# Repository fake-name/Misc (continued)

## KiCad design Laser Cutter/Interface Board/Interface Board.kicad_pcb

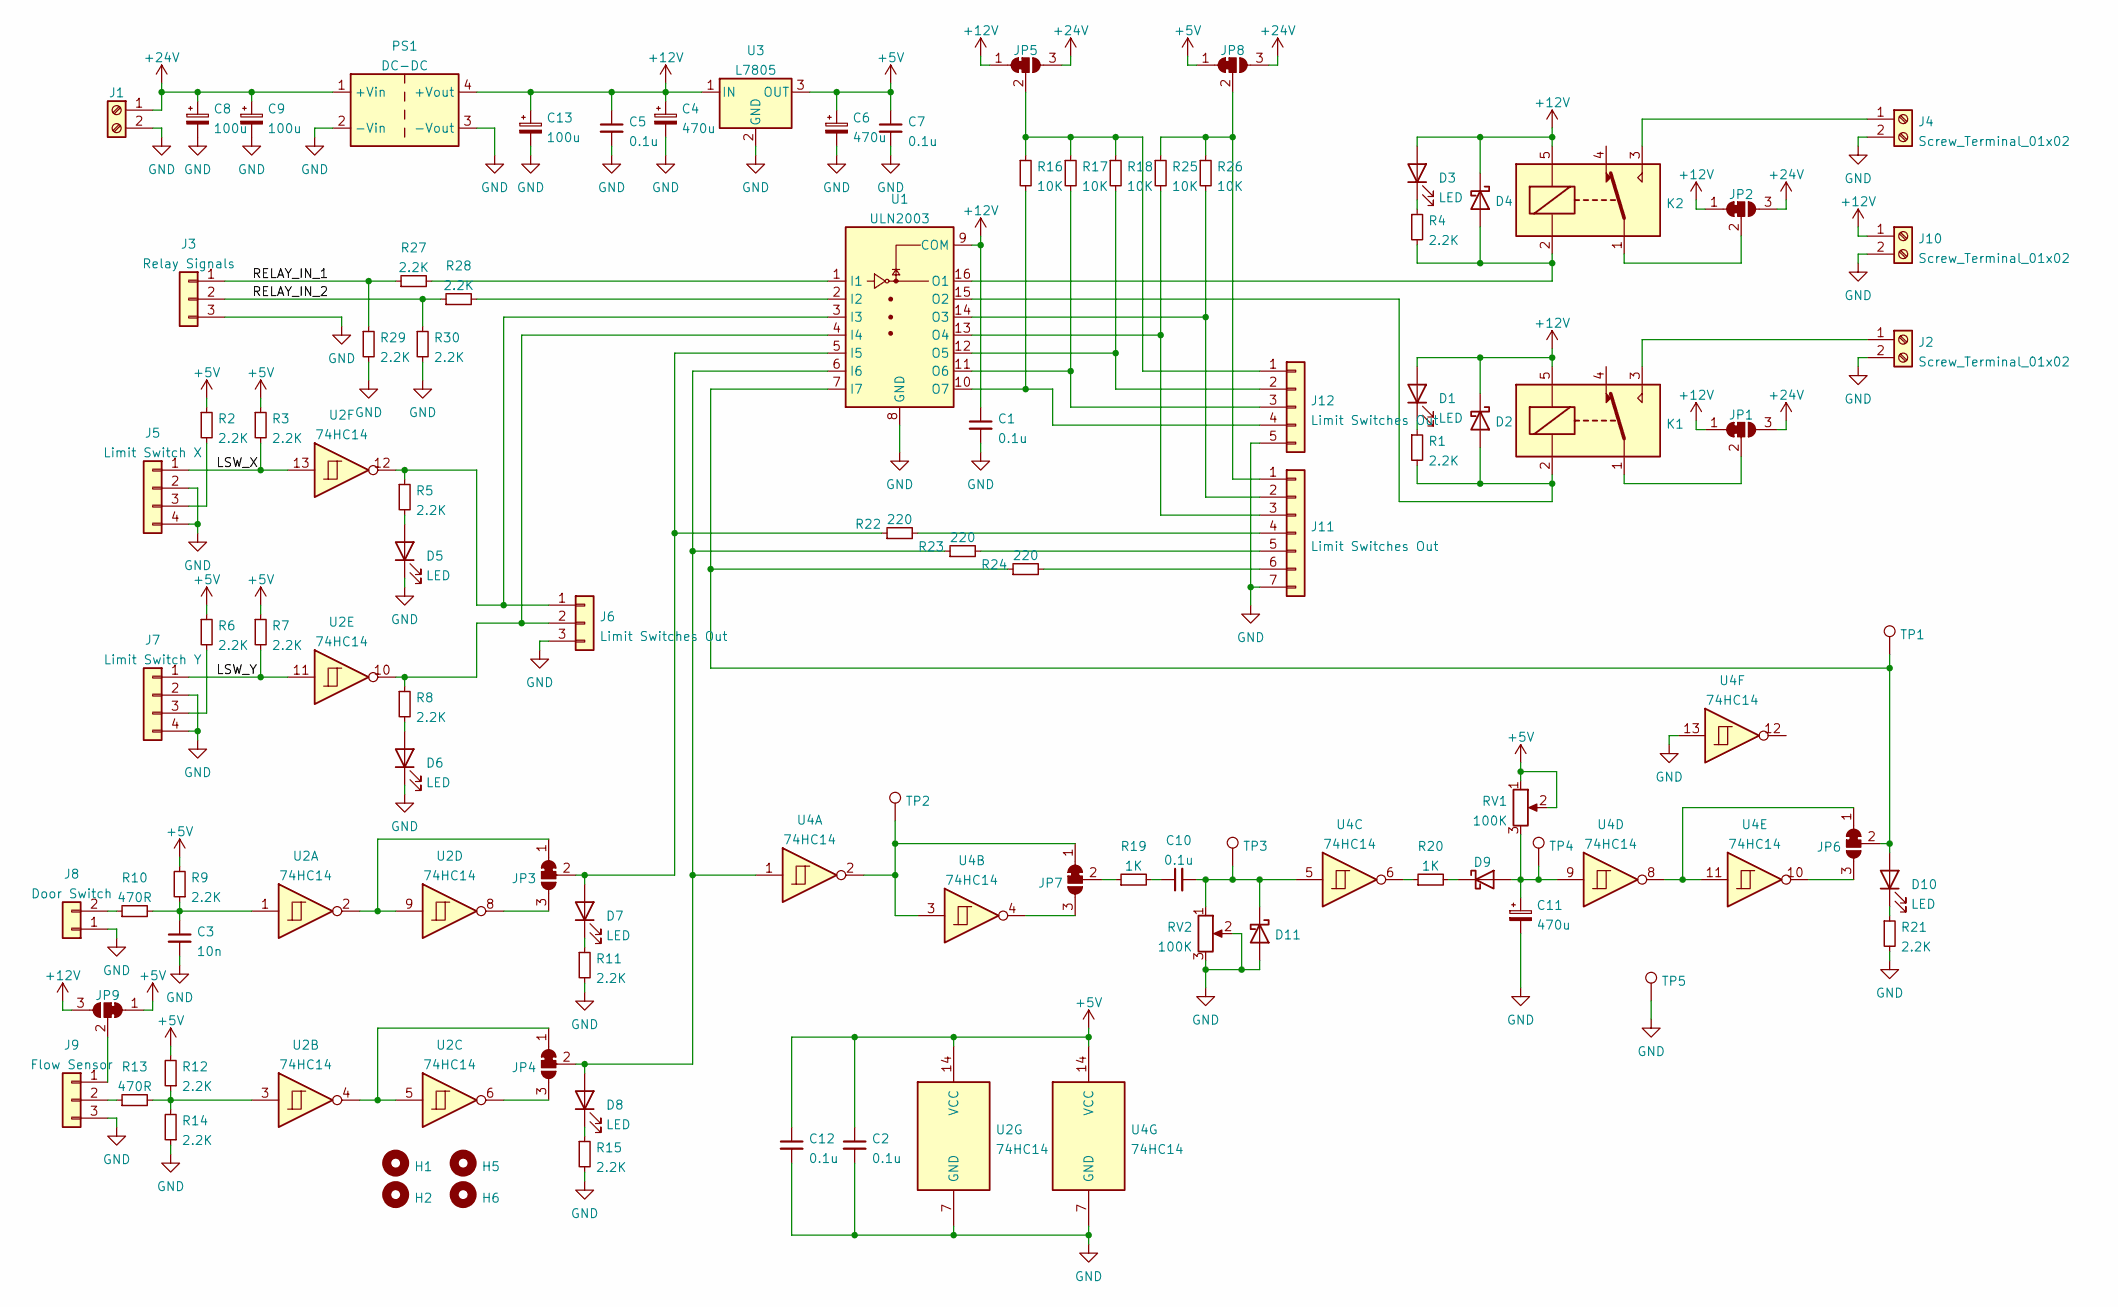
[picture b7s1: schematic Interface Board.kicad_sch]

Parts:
C1, C2, C5, C7, C10, C12: 0.1u; C_Disc_D3.8mm_W2.6mm_P2.50mm
C3: 10n; C_Disc_D3.8mm_W2.6mm_P2.50mm
C4, C6, C11: 470u; CP_Radial_D8.0mm_P3.50mm
C8, C9, C13: 100u; CP_Radial_D8.0mm_P3.50mm
D1, D3, D5, D6, D7, D8, D10: LED; LED_D5.0mm
D2, D4: B260; D_DO-15_P12.70mm_Horizontal
D9, D11: D_Schottky; D_DO-15_P12.70mm_Horizontal
H1, H2, H5, H6: MountingHole; MountingHole_3.2mm_M3_Pad_Via
J1, J2, J4, J10: Screw_Terminal_01x02; TerminalBlock_bornier-2_P5.08mm
J3: Relay Signals; JST_XH_B3B-XH-AM_1x03_P2.50mm_Vertical
J5: Limit Switch X; JST_XH_B4B-XH-AM_1x04_P2.50mm_Vertical
J6: Limit Switches Out; JST_XH_B3B-XH-AM_1x03_P2.50mm_Vertical
J7: Limit Switch Y; JST_XH_B4B-XH-AM_1x04_P2.50mm_Vertical
J8: Door Switch; JST_XH_B2B-XH-AM_1x02_P2.50mm_Vertical
J9: Flow Sensor; JST_XH_B3B-XH-AM_1x03_P2.50mm_Vertical
J11: Limit Switches Out; JST_XA_B07B-XASK-1_1x07_P2.50mm_Vertical
J12: Limit Switches Out; JST_XA_B05B-XASK-1_1x05_P2.50mm_Vertical
JP1, JP2, JP3, JP4, JP5, JP6, JP7, JP8, JP9: SolderJumper_3_Bridged12; SolderJumper-3_P1.3mm_Bridged12_Pad1.0x1.5mm_NumberLabels
K1, K2: SANYOU_SRD_Form_C; Relay_SPDT_SANYOU_SRD_Series_Form_C
PS1: DC-DC; Generic_DCDC_Red
R1, R2, R3, R4, R5, R6, R7, R8, R9, R11, R12, R14, R15, R21, R27, R28, R29, R30: 2.2K; R_Axial_DIN0204_L3.6mm_D1.6mm_P7.62mm_Horizontal
R10, R13: 470R; R_Axial_DIN0204_L3.6mm_D1.6mm_P7.62mm_Horizontal
R16, R17: 10K; R_Axial_DIN0204_L3.6mm_D1.6mm_P7.62mm_Horizontal
R18: 10K; R_Axial_DIN0204_L3.6mm_D1.6mm_P10.16mm_Horizontal
R19, R20: 1K; R_Axial_DIN0204_L3.6mm_D1.6mm_P7.62mm_Horizontal
R22, R23, R24: 220; R_Axial_DIN0204_L3.6mm_D1.6mm_P7.62mm_Horizontal
R25, R26: 10K; R_Axial_DIN0204_L3.6mm_D1.6mm_P12.7mm_Horizontal
RV1, RV2: 100K; Potentiometer_Bourns_3299Y_Vertical
TP1, TP2, TP3, TP4, TP5: TestPoint; TestPoint_Loop_D1.80mm_Drill1.0mm_Beaded
U1: ULN2003; DIP-16_W7.62mm_Socket_LongPads
U2, U4: 74HC14; DIP-14_W7.62mm_Socket_LongPads
U3: L7805; TO-220-3_Horizontal_TabDown

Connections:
+5V: C2.1, C6.1, C7.1, C12.1, JP8.1 (A), JP9.1 (A), R2.1, R3.1, R6.1, R7.1, R9.2, R12.2, RV1.1, RV1.2, U2.14 (VCC), U3.3 (OUT), U4.14 (VCC)
+12V: C1.1, C4.1, C5.1, C13.1, D1.2 (A), D2.1 (K), D3.2 (A), D4.1 (K), J10.1, JP1.1 (A), JP2.1 (A), JP5.1 (A), JP9.3 (B), K1.5, K2.5, PS1.4 (+Vout), U1.9 (COM), U3.1 (IN)
+24V: C8.1, C9.1, J1.1, JP1.3 (B), JP2.3 (B), JP5.3 (B), JP8.3 (B), PS1.1 (+Vin)
/LSW_X: J5.1, R3.2, U2.13
/LSW_Y: J7.1, R7.2, U2.11
/RELAY_IN_1: J3.1, R27.1, R29.1
/RELAY_IN_2: J3.2, R28.1, R30.1
GND: C1.2, C2.2, C3.2, C4.2, C5.2, C6.2, C7.2, C8.2, C9.2, C11.2, C12.2, C13.2, D5.1 (K), D6.1 (K), D11.2 (A), J1.2, J2.2, J3.3, J4.2, J5.2, J5.4, J6.3, J7.2, J7.4, J8.1, J9.3, J10.2, J11.7, J12.5, PS1.2 (-Vin), PS1.3 (-Vout), R11.2, R14.1, R15.2, R21.2, R29.2, R30.2, RV2.2, RV2.3, TP5.1, U1.8 (GND), U2.7 (GND), U3.2 (GND), U4.7 (GND), U4.13
unnamed: C3.1, R9.1, R10.2, U2.1
unnamed: C10.1, R19.2
unnamed: C10.2, D11.1 (K), RV2.1, TP3.1, U4.5
unnamed: C11.1, D9.2 (A), RV1.3, TP4.1, U4.9
unnamed: D1.1 (K), R1.1
unnamed: D2.2 (A), K1.2, R1.2, U1.15 (O2)
unnamed: D3.1 (K), R4.1
unnamed: D4.2 (A), K2.2, R4.2, U1.16 (O1)
unnamed: D5.2 (A), R5.2
unnamed: D6.2 (A), R8.2
unnamed: D7.1 (K), R11.1
unnamed: D7.2 (A), JP3.2 (C), R22.1, U1.5 (I5)
unnamed: D8.1 (K), R15.1
unnamed: D8.2 (A), JP4.2 (C), R23.1, U1.6 (I6), U4.1
unnamed: D9.1 (K), R20.2
unnamed: D10.1 (K), R21.1
unnamed: D10.2 (A), JP6.2 (C), R24.1, TP1.1, U1.7 (I7)
unnamed: J2.1, K1.3
unnamed: J4.1, K2.3
unnamed: J5.3, R2.2
unnamed: J6.1, R5.1, U1.3 (I3), U2.12
unnamed: J6.2, R8.1, U1.4 (I4), U2.10
unnamed: J7.3, R6.2
unnamed: J8.2, R10.1
unnamed: J9.1, JP9.2 (C)
unnamed: J9.2, R13.1
unnamed: J11.1, JP8.2 (C), R25.1, R26.1
unnamed: J11.2, R26.2, U1.14 (O3)
unnamed: J11.3, R25.2, U1.13 (O4)
unnamed: J11.4, R22.2
unnamed: J11.5, R23.2
unnamed: J11.6, R24.2
unnamed: J12.1, JP5.2 (C), R16.1, R17.1, R18.1
unnamed: J12.2, R18.2, U1.12 (O5)
unnamed: J12.3, R17.2, U1.11 (O6)
unnamed: J12.4, R16.2, U1.10 (O7)
unnamed: JP1.2 (C), K1.1
unnamed: JP2.2 (C), K2.1
unnamed: JP3.1 (A), U2.2, U2.9
unnamed: JP3.3 (B), U2.8
unnamed: JP4.1 (A), U2.4, U2.5
unnamed: JP4.3 (B), U2.6
unnamed: JP6.1 (A), U4.8, U4.11
unnamed: JP6.3 (B), U4.10
unnamed: JP7.1 (A), TP2.1, U4.2, U4.3
unnamed: JP7.2 (C), R19.1
unnamed: JP7.3 (B), U4.4
unnamed: R12.1, R13.2, R14.2, U2.3
unnamed: R20.1, U4.6
unnamed: R27.2, U1.1 (I1)
unnamed: R28.2, U1.2 (I2)

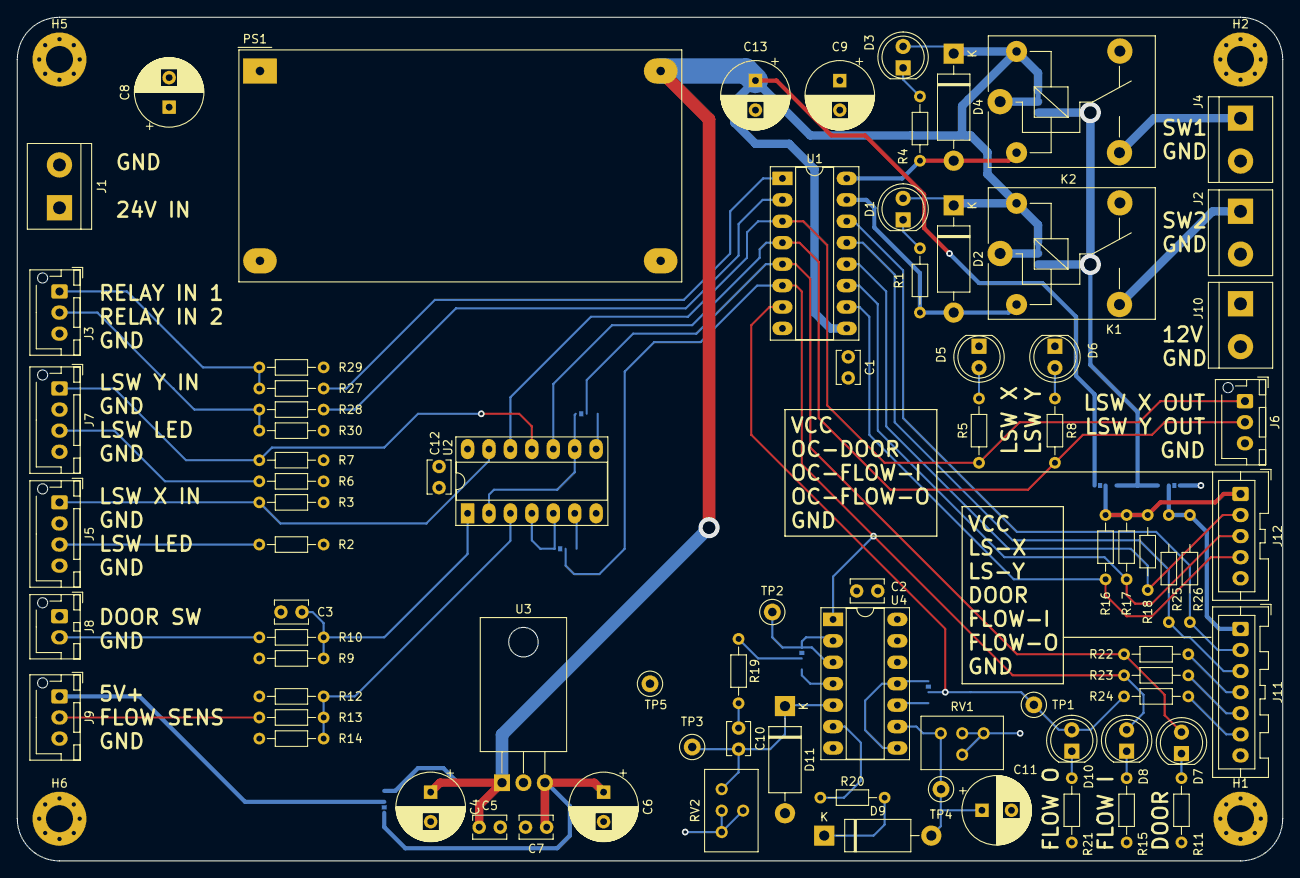
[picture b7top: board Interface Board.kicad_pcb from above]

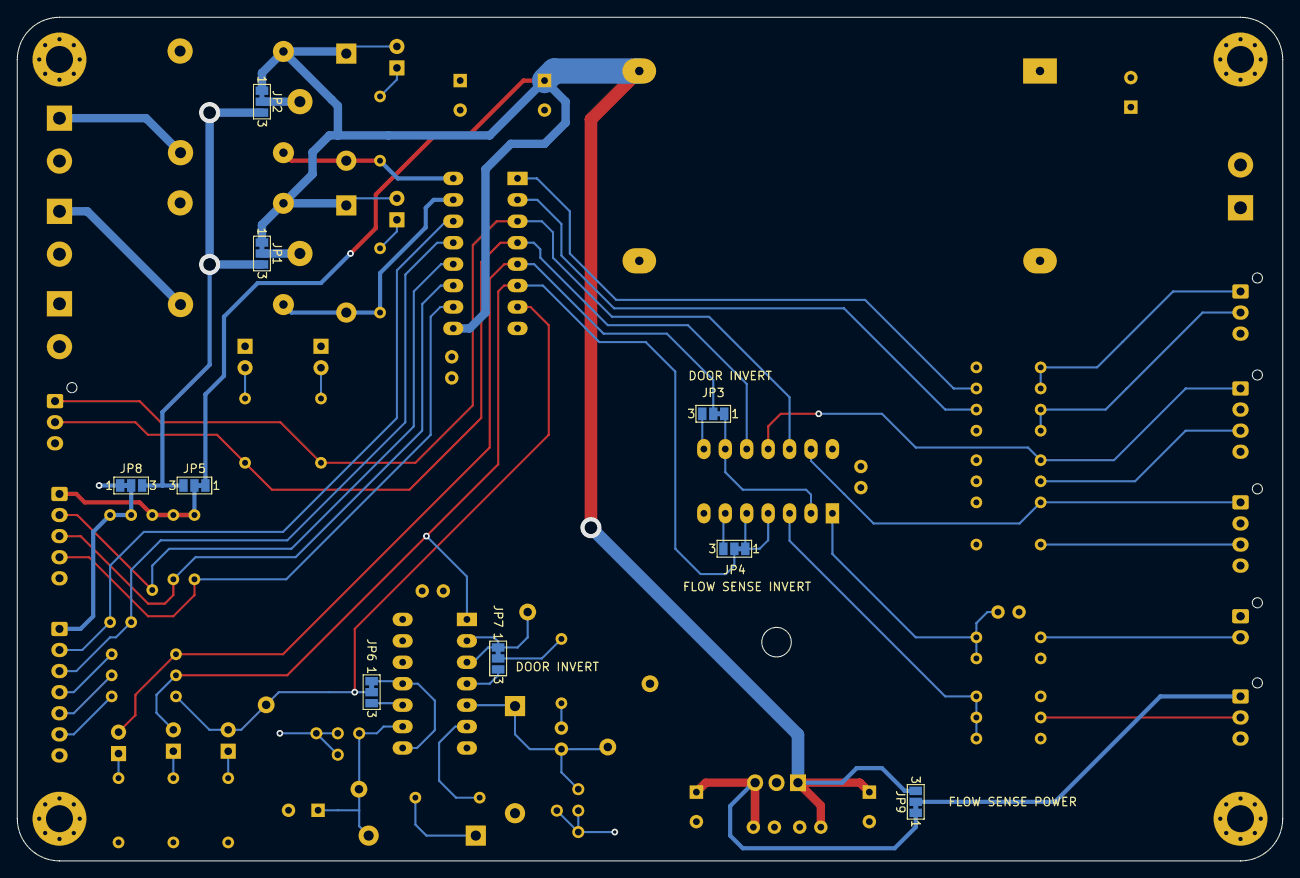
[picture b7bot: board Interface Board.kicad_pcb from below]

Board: 4 copper layers, 150.0 x 100.0 mm, 93 parts (9 on the bottom side), 59 nets.

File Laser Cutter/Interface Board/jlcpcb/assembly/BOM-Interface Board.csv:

Comment,Designator,Footprint,LCSC
2.2K,R1,R_Axial_DIN0204_L3.6mm_D1.6mm_P7.62mm_Horizontal,
10K,R26,R_Axial_DIN0204_L3.6mm_D1.6mm_P12.7mm_Horizontal,
LED,D3,LED_D5.0mm,
Limit Switches Out,J12,JST_XA_B05B-XASK-1_1x05_P2.50mm_Vertical,
2.2K,R9,R_Axial_DIN0204_L3.6mm_D1.6mm_P7.62mm_Horizontal,
470u,C11,CP_Radial_D8.0mm_P3.50mm,
0.1u,C2,C_Disc_D3.8mm_W2.6mm_P2.50mm,
Screw_Terminal_01x02,J4,TerminalBlock_bornier-2_P5.08mm,
D_Schottky,D9,D_DO-15_P12.70mm_Horizontal,
470R,R10,R_Axial_DIN0204_L3.6mm_D1.6mm_P7.62mm_Horizontal,
2.2K,R5,R_Axial_DIN0204_L3.6mm_D1.6mm_P7.62mm_Horizontal,
100u,C8,CP_Radial_D8.0mm_P3.50mm,
100K,RV1,Potentiometer_Bourns_3299Y_Vertical,
TestPoint,TP5,TestPoint_Loop_D1.80mm_Drill1.0mm_Beaded,
10K,R16,R_Axial_DIN0204_L3.6mm_D1.6mm_P7.62mm_Horizontal,
DC-DC,PS1,Generic_DCDC_Red,
1K,R19,R_Axial_DIN0204_L3.6mm_D1.6mm_P7.62mm_Horizontal,
1K,R20,R_Axial_DIN0204_L3.6mm_D1.6mm_P7.62mm_Horizontal,
2.2K,R8,R_Axial_DIN0204_L3.6mm_D1.6mm_P7.62mm_Horizontal,
LED,D7,LED_D5.0mm,
2.2K,R11,R_Axial_DIN0204_L3.6mm_D1.6mm_P7.62mm_Horizontal,
2.2K,R15,R_Axial_DIN0204_L3.6mm_D1.6mm_P7.62mm_Horizontal,
10K,R25,R_Axial_DIN0204_L3.6mm_D1.6mm_P12.7mm_Horizontal,
TestPoint,TP4,TestPoint_Loop_D1.80mm_Drill1.0mm_Beaded,
L7805,U3,TO-220-3_Horizontal_TabDown,
SANYOU_SRD_Form_C,K2,Relay_SPDT_SANYOU_SRD_Series_Form_C,
470R,R13,R_Axial_DIN0204_L3.6mm_D1.6mm_P7.62mm_Horizontal,
ULN2003,U1,DIP-16_W7.62mm_Socket_LongPads,
B260,D4,D_DO-15_P12.70mm_Horizontal,
2.2K,R12,R_Axial_DIN0204_L3.6mm_D1.6mm_P7.62mm_Horizontal,
D_Schottky,D11,D_DO-15_P12.70mm_Horizontal,
Relay Signals,J3,JST_XH_B3B-XH-AM_1x03_P2.50mm_Vertical,
10n,C3,C_Disc_D3.8mm_W2.6mm_P2.50mm,
470u,C6,CP_Radial_D8.0mm_P3.50mm,
220,R23,R_Axial_DIN0204_L3.6mm_D1.6mm_P7.62mm_Horizontal,
LED,D5,LED_D5.0mm,
TestPoint,TP3,TestPoint_Loop_D1.80mm_Drill1.0mm_Beaded,
100K,RV2,Potentiometer_Bourns_3299Y_Vertical,
2.2K,R29,R_Axial_DIN0204_L3.6mm_D1.6mm_P7.62mm_Horizontal,
SANYOU_SRD_Form_C,K1,Relay_SPDT_SANYOU_SRD_Series_Form_C,
Screw_Terminal_01x02,J2,TerminalBlock_bornier-2_P5.08mm,
MountingHole,H5,MountingHole_3.2mm_M3_Pad_Via,
Limit Switch Y,J7,JST_XH_B4B-XH-AM_1x04_P2.50mm_Vertical,
LED,D6,LED_D5.0mm,
2.2K,R28,R_Axial_DIN0204_L3.6mm_D1.6mm_P7.62mm_Horizontal,
2.2K,R14,R_Axial_DIN0204_L3.6mm_D1.6mm_P7.62mm_Horizontal,
MountingHole,H2,MountingHole_3.2mm_M3_Pad_Via,
74HC14,U2,DIP-14_W7.62mm_Socket_LongPads,
0.1u,C1,C_Disc_D3.8mm_W2.6mm_P2.50mm,
TestPoint,TP1,TestPoint_Loop_D1.80mm_Drill1.0mm_Beaded,
Limit Switch X,J5,JST_XH_B4B-XH-AM_1x04_P2.50mm_Vertical,
2.2K,R3,R_Axial_DIN0204_L3.6mm_D1.6mm_P7.62mm_Horizontal,
220,R24,R_Axial_DIN0204_L3.6mm_D1.6mm_P7.62mm_Horizontal,
220,R22,R_Axial_DIN0204_L3.6mm_D1.6mm_P7.62mm_Horizontal,
2.2K,R21,R_Axial_DIN0204_L3.6mm_D1.6mm_P7.62mm_Horizontal,
0.1u,C5,C_Disc_D3.8mm_W2.6mm_P2.50mm,
2.2K,R2,R_Axial_DIN0204_L3.6mm_D1.6mm_P7.62mm_Horizontal,
Screw_Terminal_01x02,J10,TerminalBlock_bornier-2_P5.08mm,
100u,C13,CP_Radial_D8.0mm_P3.50mm,
Limit Switches Out,J11,JST_XA_B07B-XASK-1_1x07_P2.50mm_Vertical,
Limit Switches Out,J6,JST_XH_B3B-XH-AM_1x03_P2.50mm_Vertical,
74HC14,U4,DIP-14_W7.62mm_Socket_LongPads,
2.2K,R4,R_Axial_DIN0204_L3.6mm_D1.6mm_P7.62mm_Horizontal,
470u,C4,CP_Radial_D8.0mm_P3.50mm,
0.1u,C12,C_Disc_D3.8mm_W2.6mm_P2.50mm,
2.2K,R30,R_Axial_DIN0204_L3.6mm_D1.6mm_P7.62mm_Horizontal,
10K,R18,R_Axial_DIN0204_L3.6mm_D1.6mm_P10.16mm_Horizontal,
TestPoint,TP2,TestPoint_Loop_D1.80mm_Drill1.0mm_Beaded,
2.2K,R7,R_Axial_DIN0204_L3.6mm_D1.6mm_P7.62mm_Horizontal,
LED,D8,LED_D5.0mm,
100u,C9,CP_Radial_D8.0mm_P3.50mm,
2.2K,R6,R_Axial_DIN0204_L3.6mm_D1.6mm_P7.62mm_Horizontal,
Screw_Terminal_01x02,J1,TerminalBlock_bornier-2_P5.08mm,
MountingHole,H6,MountingHole_3.2mm_M3_Pad_Via,
LED,D1,LED_D5.0mm,
Flow Sensor,J9,JST_XH_B3B-XH-AM_1x03_P2.50mm_Vertical,
Door Switch,J8,JST_XH_B2B-XH-AM_1x02_P2.50mm_Vertical,
2.2K,R27,R_Axial_DIN0204_L3.6mm_D1.6mm_P7.62mm_Horizontal,
0.1u,C7,C_Disc_D3.8mm_W2.6mm_P2.50mm,
MountingHole,H1,MountingHole_3.2mm_M3_Pad_Via,
B260,D2,D_DO-15_P12.70mm_Horizontal,
LED,D10,LED_D5.0mm,
10K,R17,R_Axial_DIN0204_L3.6mm_D1.6mm_P7.62mm_Horizontal,
0.1u,C10,C_Disc_D3.8mm_W2.6mm_P2.50mm,
SolderJumper_3_Bridged12,JP3,SolderJumper-3_P1.3mm_Bridged12_Pad1.0x1.5mm_NumberLabels,
SolderJumper_3_Bridged12,JP1,SolderJumper-3_P1.3mm_Bridged12_Pad1.0x1.5mm_NumberLabels,
SolderJumper_3_Bridged12,JP2,SolderJumper-3_P1.3mm_Bridged12_Pad1.0x1.5mm_NumberLabels,
SolderJumper_3_Bridged12,JP7,SolderJumper-3_P1.3mm_Bridged12_Pad1.0x1.5mm_NumberLabels,
SolderJumper_3_Bridged12,JP5,SolderJumper-3_P1.3mm_Bridged12_Pad1.0x1.5mm_NumberLabels,
SolderJumper_3_Bridged12,JP4,SolderJumper-3_P1.3mm_Bridged12_Pad1.0x1.5mm_NumberLabels,
SolderJumper_3_Bridged12,JP9,SolderJumper-3_P1.3mm_Bridged12_Pad1.0x1.5mm_NumberLabels,
SolderJumper_3_Bridged12,JP6,SolderJumper-3_P1.3mm_Bridged12_Pad1.0x1.5mm_NumberLabels,
SolderJumper_3_Bridged12,JP8,SolderJumper-3_P1.3mm_Bridged12_Pad1.0x1.5mm_NumberLabels,

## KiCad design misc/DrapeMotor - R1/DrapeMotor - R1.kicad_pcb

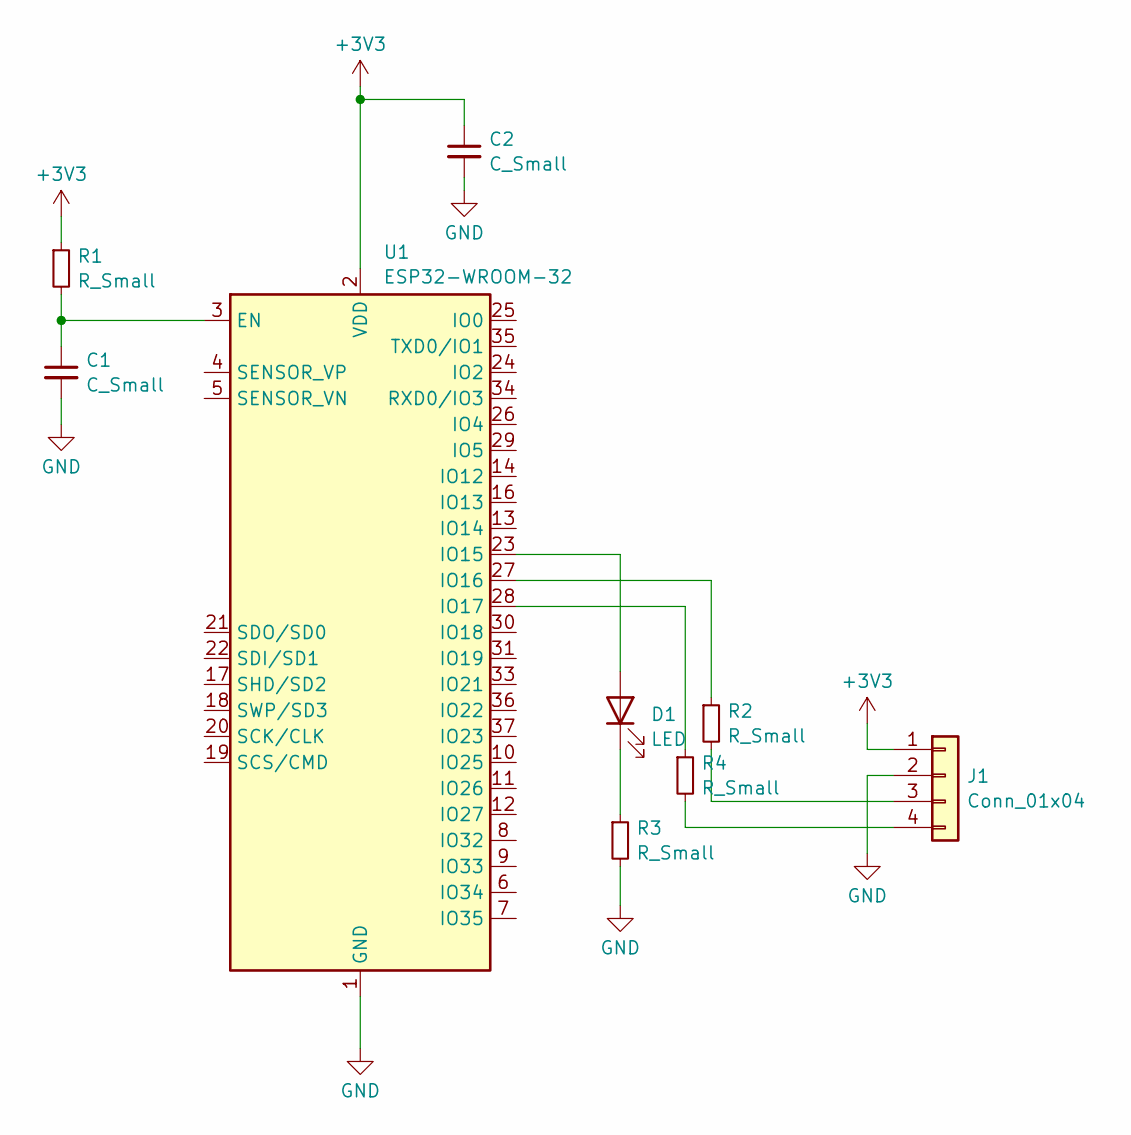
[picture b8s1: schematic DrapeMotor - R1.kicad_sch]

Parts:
C1, C2: C_Small; C_1206_3216Metric_Pad1.33x1.80mm_HandSolder
D1: LED; D_1206_3216Metric_Pad1.42x1.75mm_HandSolder
J1: Conn_01x04; PinSocket_1x04_P2.54mm_Vertical
R1, R2, R3, R4: R_Small; R_1206_3216Metric_Pad1.30x1.75mm_HandSolder
U1: ESP32-WROOM-32

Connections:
+3V3: C2.1, J1.1, R1.1, U1.2 (VDD)
GND: C1.2, C2.2, J1.2, R3.2, U1.1 (GND), U1.15 (GND), U1.38 (GND), U1.39 (GND)
unnamed: D1.2 (A), U1.23 (IO15)
unnamed: D1.1 (K), R3.1
unnamed: J1.3, R2.2
unnamed: J1.4, R4.2
unnamed: C1.1, R1.2, U1.3 (EN)
unnamed: R2.1, U1.27 (IO16)
unnamed: R4.1, U1.28 (IO17)

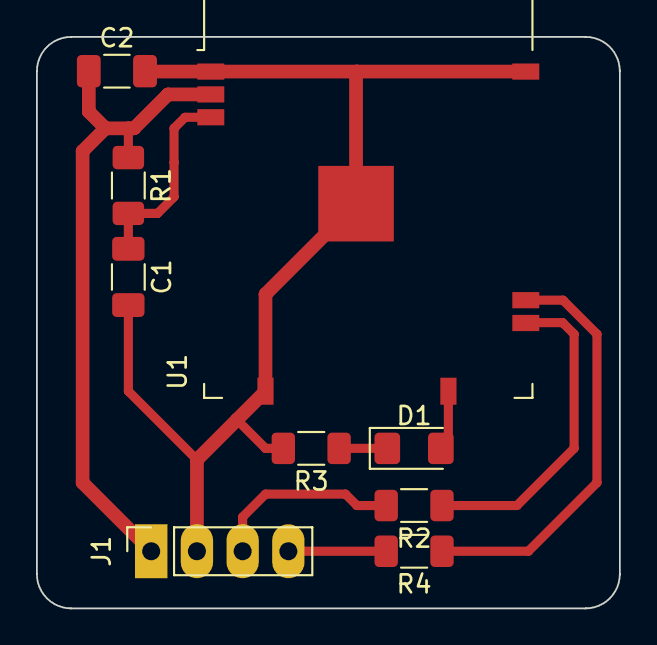
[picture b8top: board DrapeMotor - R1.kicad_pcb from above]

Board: 2 copper layers, 32.4 x 31.8 mm, 9 parts (0 on the bottom side), 9 nets.
